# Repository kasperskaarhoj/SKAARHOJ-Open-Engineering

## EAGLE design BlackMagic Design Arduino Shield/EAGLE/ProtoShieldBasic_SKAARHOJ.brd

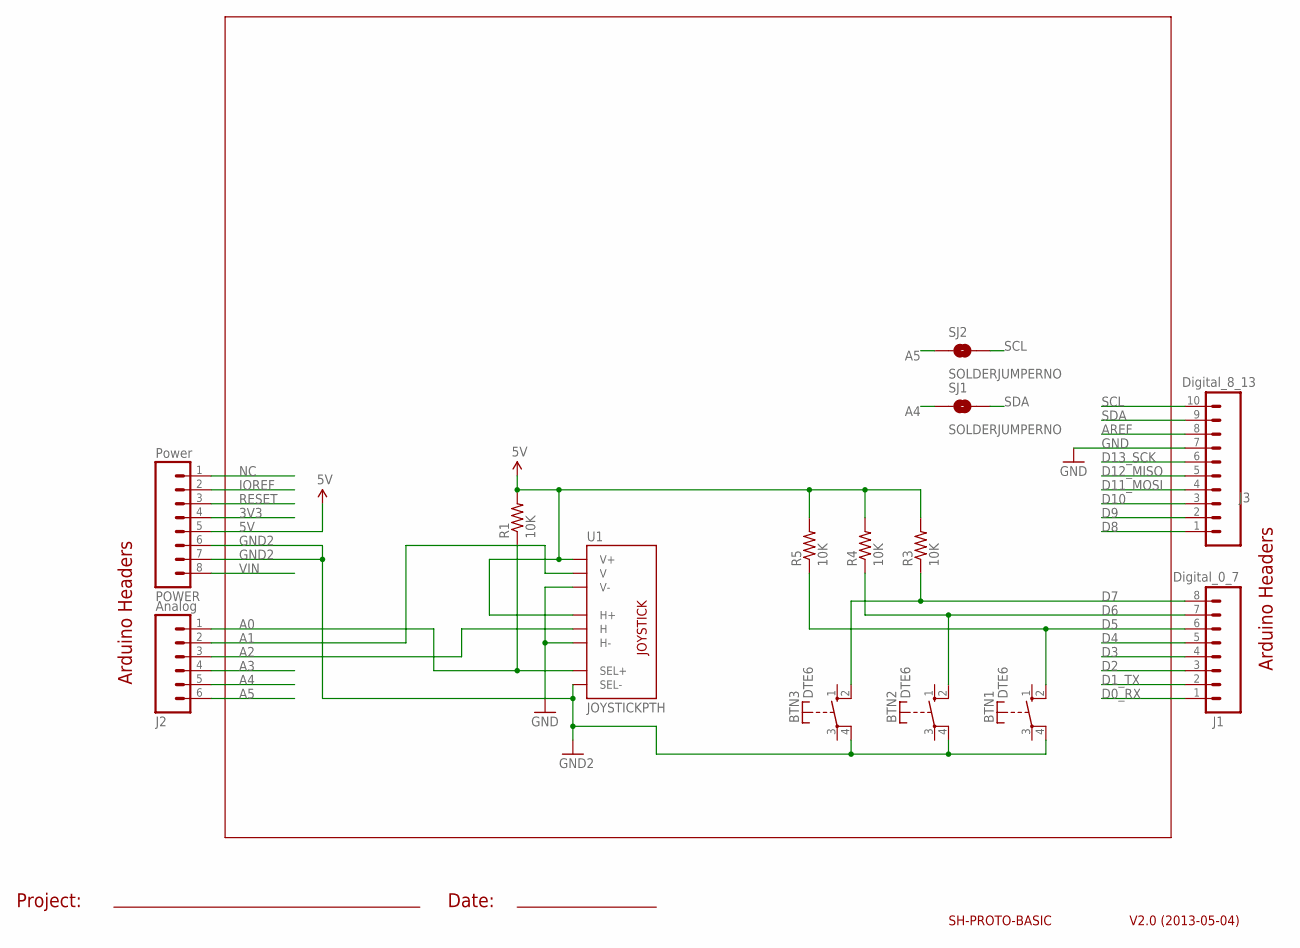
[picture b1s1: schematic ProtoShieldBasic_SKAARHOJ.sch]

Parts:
BTN1, BTN2, BTN3: DTE6
J1: Digital_0_7; 1X08
J2: Analog; 1X06
J3: Digital_8_13; 1X10
POWER: Power; 1X08
R1, R3, R4, R5: 10K; 0207/10
SJ1, SJ2: SOLDERJUMPERNO; SJ_2S-NO
U1: JOYSTICKPTH; JOYSTICK

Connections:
3V3: POWER.4
5V: POWER.5, R1.2, R3.2, R4.2, R5.2, U1.H1 (H+), U1.V1 (V+)
A0: J2.1, R1.1, U1.B1A (SEL+)
A1: J2.2, U1.V2 (V)
A2: J2.3, U1.H2 (H)
A3: J2.4
A4: J2.5, SJ1.1
A5: J2.6, SJ2.1
AREF: J3.8
D0_RX: J1.1
D1_TX: J1.2
D2: J1.3
D3: J1.4
D4: J1.5
D5: BTN1.2 (S), J1.6, R5.1
D6: BTN2.2 (S), J1.7, R4.1
D7: BTN3.2 (S), J1.8, R3.1
D8: J3.1
D9: J3.2
D10: J3.3
D11_MOSI: J3.4
D12_MISO: J3.5
D13_SCK: J3.6
GND: J3.7, U1.H3 (H-), U1.V3 (V-)
GND2: BTN1.4, BTN2.4, BTN3.4, POWER.6, POWER.7, U1.B2A (SEL-)
IOREF: POWER.2
NC: POWER.1
RESET: POWER.3
SCL: J3.10, SJ2.2
SDA: J3.9, SJ1.2
VIN: POWER.8

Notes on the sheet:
V2.0 (2013-05-04)
SH-PROTO-BASIC
Arduino Headers
Project:
Date:

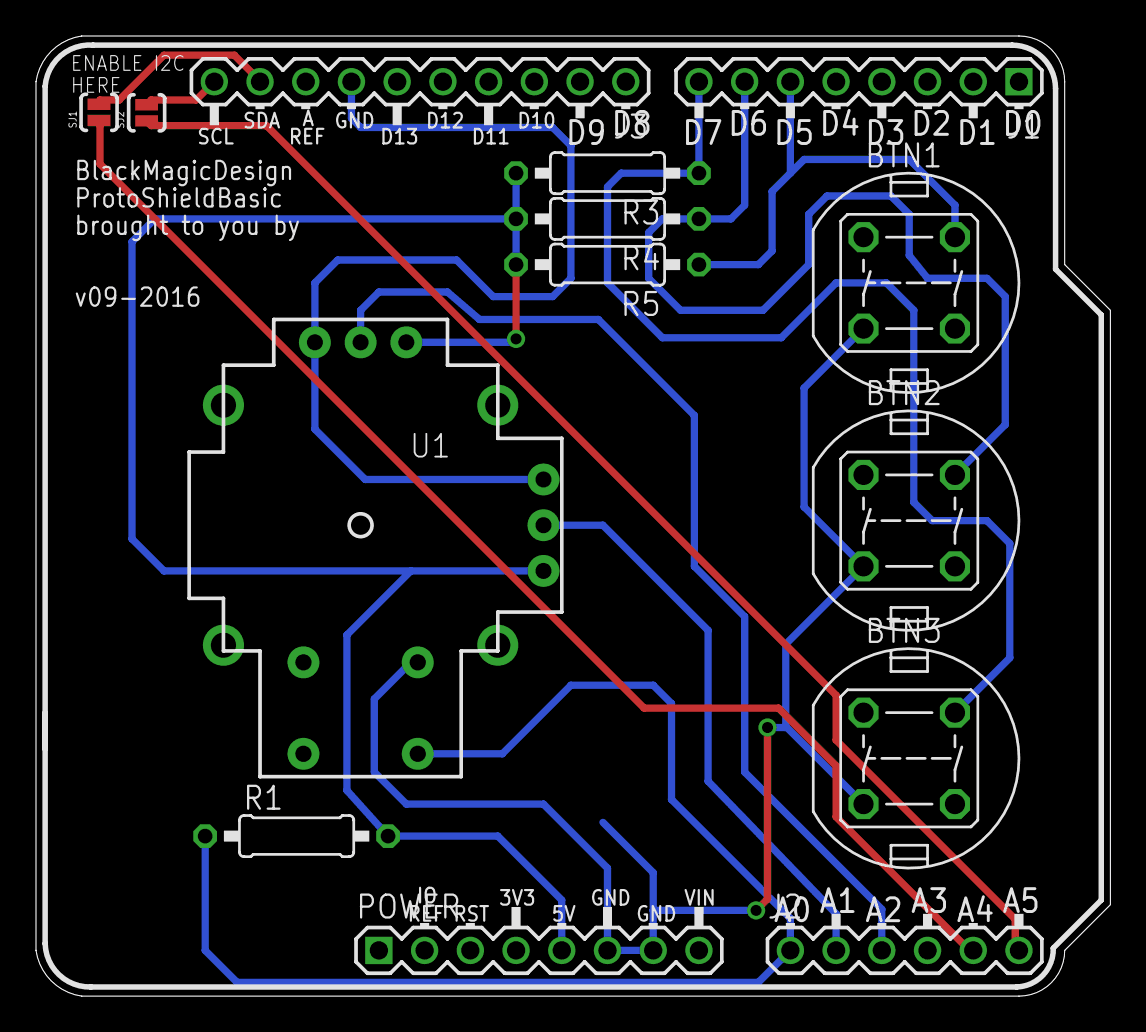
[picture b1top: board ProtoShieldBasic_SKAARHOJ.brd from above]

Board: 2 copper layers, 59.7 x 53.3 mm, 14 parts (0 on the bottom side), 13 nets.

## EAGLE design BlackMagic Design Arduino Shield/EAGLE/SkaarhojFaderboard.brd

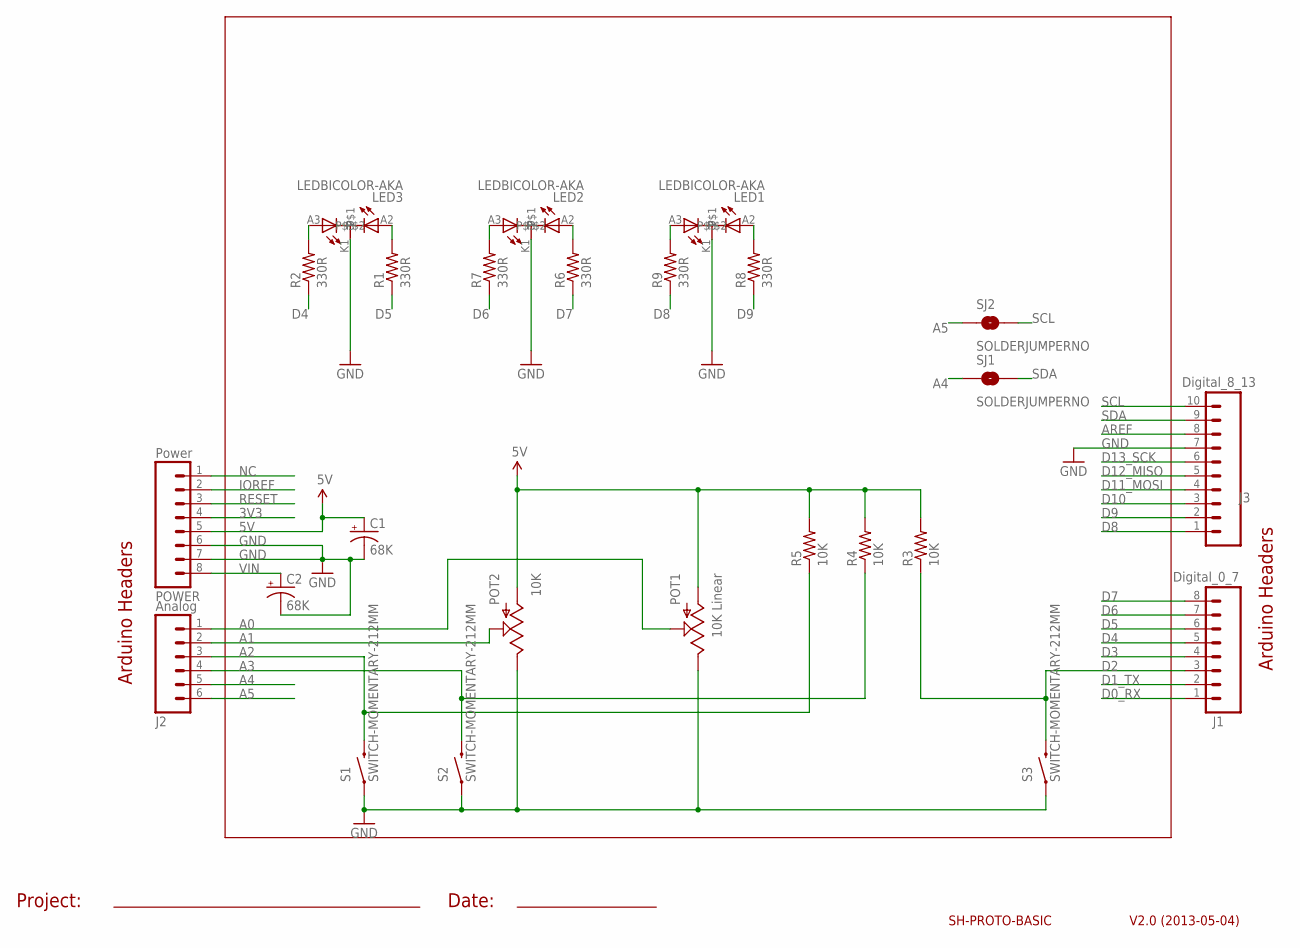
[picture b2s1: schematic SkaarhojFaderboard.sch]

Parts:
C1, C2: 68K; CPOL-RADIAL-100UF-25V
J1: Digital_0_7; 1X08
J2: Analog; 1X06
J3: Digital_8_13; 1X10
LED1, LED2, LED3: LEDBICOLOR-AKA; LED5MM-BICOLOR
POT1: 10K Linear; SLIDER20
POT2: 10K; ALPS_POT
POWER: Power; 1X08
R1, R2, R6, R7, R8, R9: 330R; 0207/10
R3, R4, R5: 10K; 0207/10
S1, S2, S3: SWITCH-MOMENTARY-212MM; TACTILE-PTH-12MM
SJ1, SJ2: SOLDERJUMPERNO; SJ_2S-NO

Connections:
3V3: POWER.4
5V: C1.1 (+), POT1.3 (A), POT2.P$3 (A), POWER.5, R3.2, R4.2, R5.2
A0: J2.1, POT1.2A (S)
A1: J2.2, POT2.P$2 (S)
A2: J2.3, R5.1, S1.3 (2)
A3: J2.4, R4.1, S2.3 (2)
A4: J2.5, SJ1.1
A5: J2.6, SJ2.1
AREF: J3.8
D0_RX: J1.1
D1_TX: J1.2
D2: J1.3, R3.1, S3.3 (2)
D3: J1.4
D4: J1.5, R2.1
D5: J1.6, R1.1
D6: J1.7, R7.1
D7: J1.8, R6.1
D8: J3.1, R9.1
D9: J3.2, R8.1
D10: J3.3
D11_MOSI: J3.4
D12_MISO: J3.5
D13_SCK: J3.6
GND: C1.2 (-), C2.2 (-), J3.7, LED1.K1, LED2.K1, LED3.K1, POT1.1 (E), POT2.P$1 (E), POWER.6, POWER.7, S1.1, S2.1, S3.1
IOREF: POWER.2
unnamed: LED2.A3, R7.2
unnamed: LED3.A3, R2.2
unnamed: LED2.A2, R6.2
unnamed: LED3.A2, R1.2
unnamed: LED1.A3, R9.2
unnamed: LED1.A2, R8.2
NC: POWER.1
RESET: POWER.3
SCL: J3.10, SJ2.2
SDA: J3.9, SJ1.2
VIN: C2.1 (+), POWER.8

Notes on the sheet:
V2.0 (2013-05-04)
SH-PROTO-BASIC
Arduino Headers
Project:
Date:

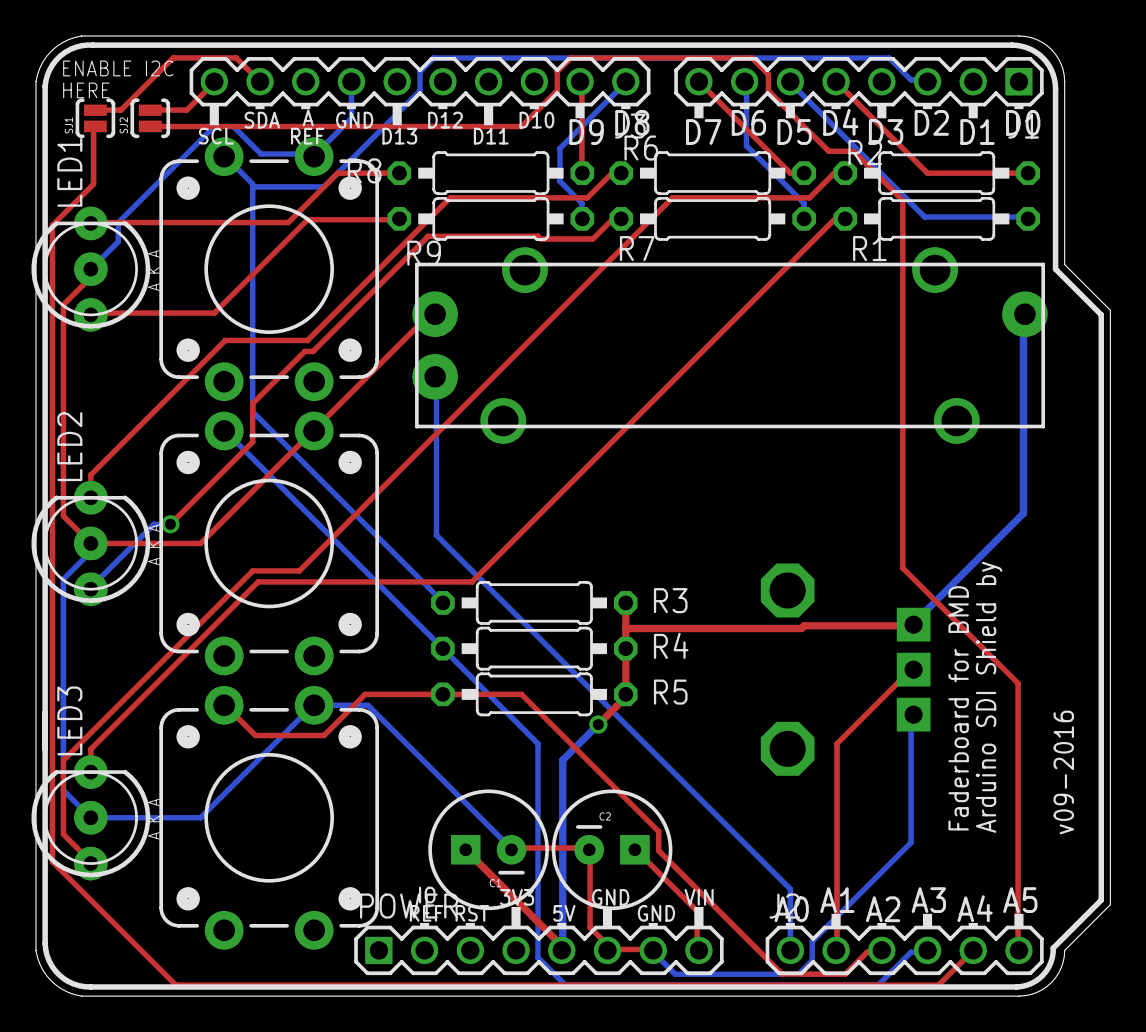
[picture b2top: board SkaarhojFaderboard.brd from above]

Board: 2 copper layers, 59.7 x 53.3 mm, 25 parts (0 on the bottom side), 24 nets.

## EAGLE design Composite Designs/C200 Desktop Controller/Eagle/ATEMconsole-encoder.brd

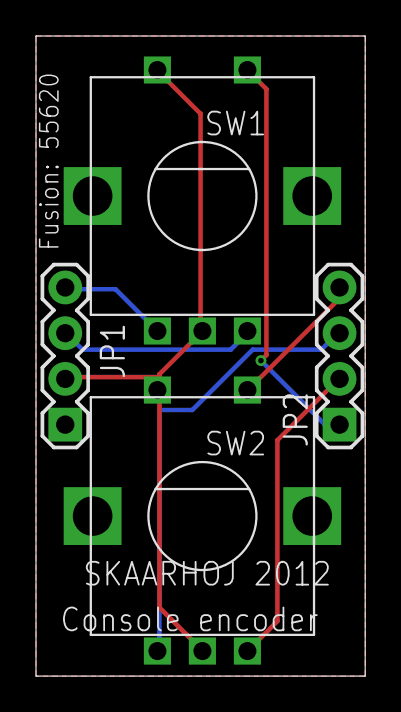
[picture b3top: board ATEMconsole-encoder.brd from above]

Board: 2 copper layers, 18.3 x 35.6 mm, 4 parts (0 on the bottom side), 7 nets.

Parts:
JP1, JP2: 1X04
SW1, SW2: EC12E_SW; ALPS_EC12E_SW

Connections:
5V: JP1.2, SW1.C, SW1.D, SW2.C, SW2.D
JP1: JP2.2, SW2.B
unnamed: JP1.3, SW1.B
unnamed: JP1.4, SW1.A
unnamed: JP2.1, SW1.E
unnamed: JP2.3, SW2.A
unnamed: JP2.4, SW2.E

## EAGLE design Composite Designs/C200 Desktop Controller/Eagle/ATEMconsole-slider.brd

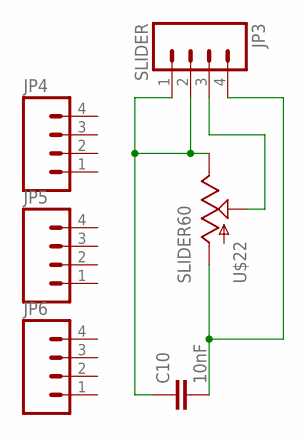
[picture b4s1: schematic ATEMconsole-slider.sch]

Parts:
C10: 10nF; AXIAL-5MM
JP3: SLIDER; 1X04
JP4, JP5, JP6: M04PTH; 1X04
U$22: SLIDER60

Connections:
unnamed: C10.P$1 (1), JP3.1, JP3.2, U$22.1 (E)
unnamed: C10.P$2 (2), JP3.4, U$22.3 (A)
unnamed: JP3.3, U$22.2A (S)

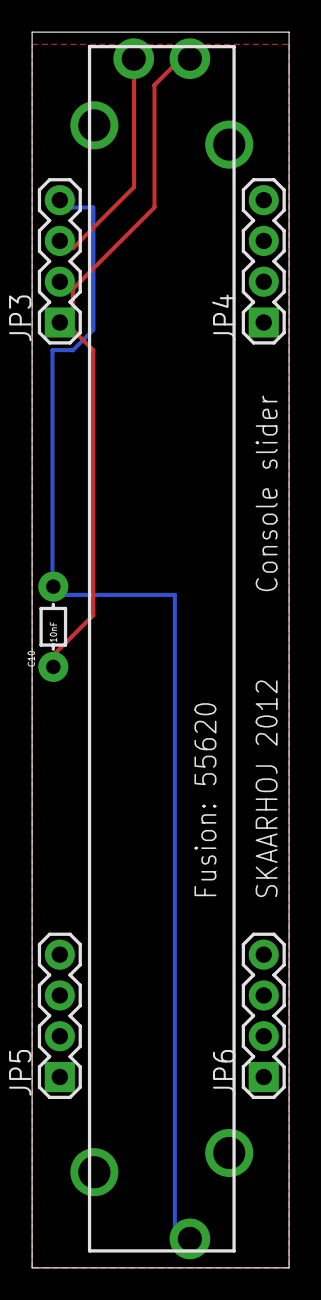
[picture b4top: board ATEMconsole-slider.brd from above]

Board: 2 copper layers, 16.0 x 77.0 mm, 6 parts (0 on the bottom side), 3 nets.

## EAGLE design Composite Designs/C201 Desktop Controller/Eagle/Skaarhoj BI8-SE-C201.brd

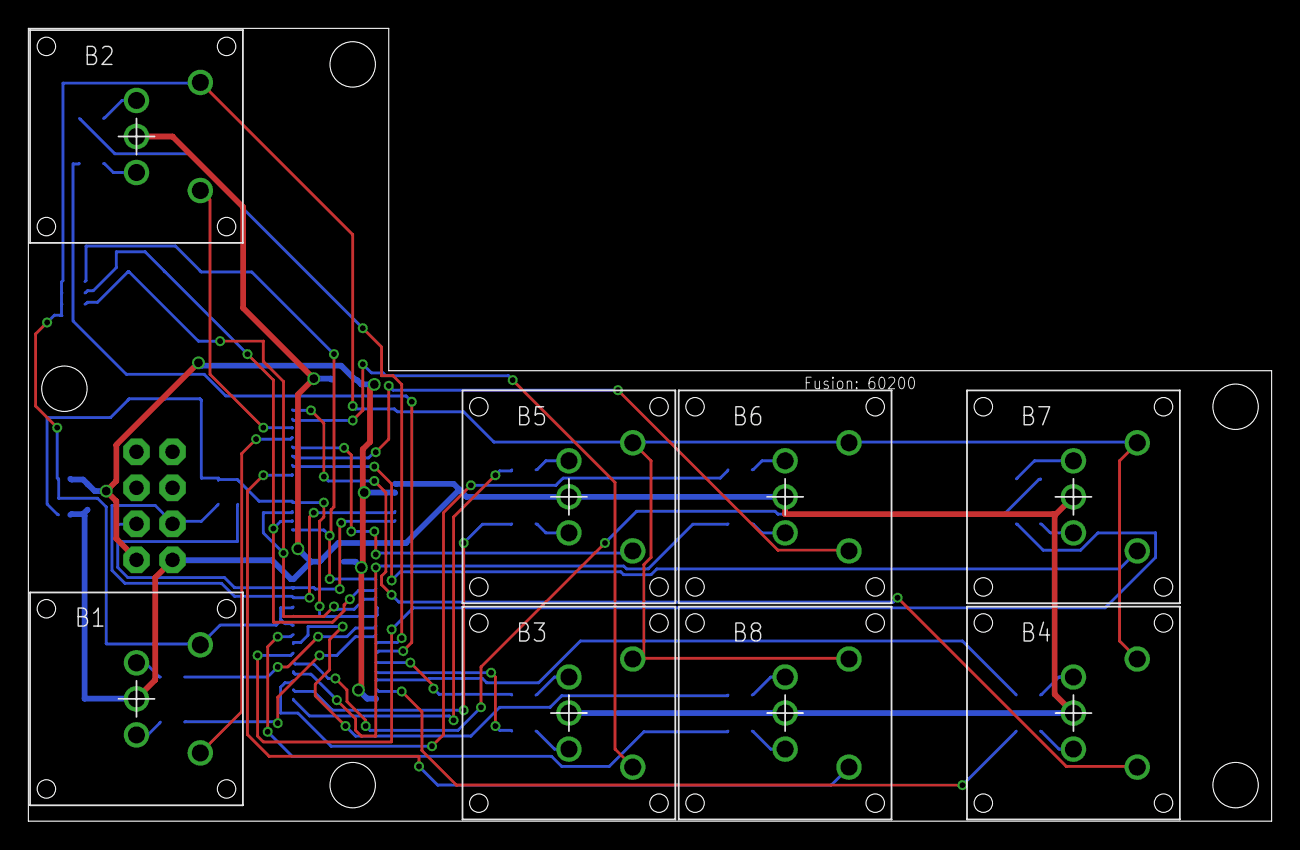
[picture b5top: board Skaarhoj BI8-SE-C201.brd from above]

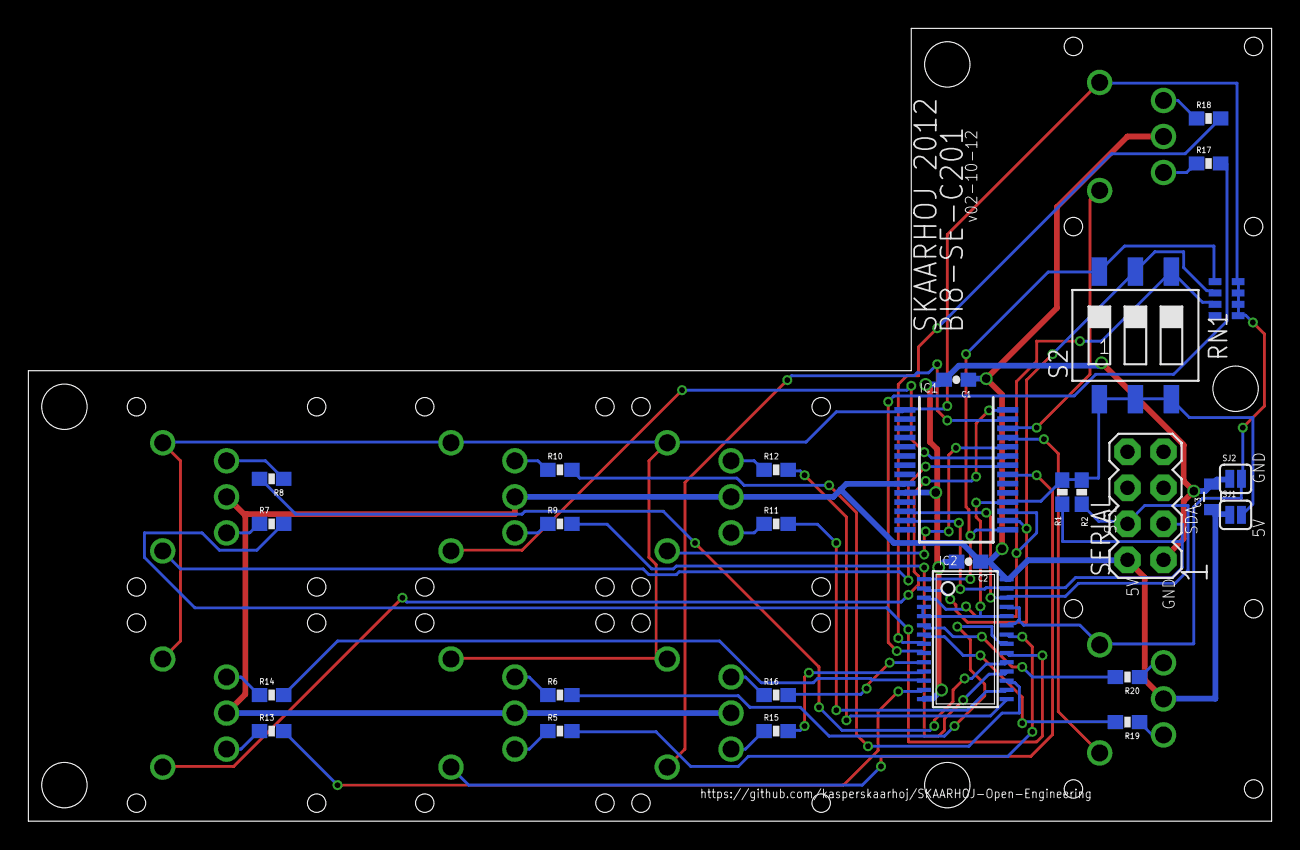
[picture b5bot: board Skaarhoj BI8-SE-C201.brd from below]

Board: 2 copper layers, 87.6 x 55.9 mm, 36 parts (28 on the bottom side), 49 nets.

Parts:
B1, B2, B3, B4, B5, B6, B7, B8: LP11-B"; LP11
C1, C2: 100nF; 0603-CAP
C3: 10uF; 0805
IC1: MCP23017SS; SSOP28
IC2: PCA9685; TSSOP28
R1, R2: 10K; 0603-RES
R5, R6, R7, R8, R9, R10, R11, R12, R13, R14, R15, R16, R17, R18, R19, R20: 270; 0603-RES
RN1: 10K; CAY16_HAND
S2: SWS003; SMS-003
SERIAL: M04X2; 2X4
SJ1, SJ2: SOLDERJUMPERNC; SJ_2S

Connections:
5V: B1.COM, B2.COM, B3.COM, B4.COM, B5.COM, B6.COM, B7.COM, B8.COM, C1.2, C2.1, C3.1, IC1.9, IC2.28, SERIAL.2, SJ1.1
5VL: IC1.18, IC2.4, IC2.5, IC2.24, R1.1, R2.1, S2.1, S2.2, S2.3, SJ1.2
A0: IC1.15, IC2.1, RN1.5, S2.6
A1: IC1.16, IC2.2, RN1.6, S2.5
A2: IC1.17, IC2.3, RN1.7, S2.4
GND: C1.1, C2.2, C3.2, IC1.10, IC2.14, SERIAL.1, SJ2.1
GNDL: B1.P$4, B2.P$4, B3.P$4, B4.P$4, B5.P$4, B6.P$4, B7.P$4, B8.P$4, IC1.1, IC2.23, IC2.25, RN1.1, RN1.2, RN1.3, RN1.4, SJ2.2
GPA0: B8.P$5, IC1.21
GPA1: B7.P$5, IC1.22
GPA2: B6.P$5, IC1.23
GPA3: B5.P$5, IC1.24
GPA4: B1.P$5, IC1.25
GPA5: B2.P$5, IC1.26
GPA6: B3.P$5, IC1.27
GPA7: B4.P$5, IC1.28
I2C_SCL: IC1.12, IC2.26, R2.2, SERIAL.4
I2C_SDA: IC1.13, IC2.27, R1.2, SERIAL.3
L0: B1.P$2, R20.1
L1: B1.P$3, R19.1
L2: B2.P$2, R18.1
L3: B2.P$3, R17.1
L4: B3.P$2, R16.1
L5: B3.P$3, R15.1
L6: B4.P$2, R14.1
L7: B4.P$3, R13.1
L8: B5.P$2, R12.1
L9: B5.P$3, R11.1
L10: B6.P$2, R10.1
L11: B6.P$3, R9.1
L12: B7.P$2, R8.1
L13: B7.P$3, R7.1
L14: B8.P$2, R6.1
L15: B8.P$3, R5.1
unnamed: IC2.13, R13.2
unnamed: IC2.12, R14.2
unnamed: IC2.11, R15.2
unnamed: IC2.10, R16.2
unnamed: IC2.9, R17.2
unnamed: IC2.8, R18.2
unnamed: IC2.7, R19.2
unnamed: IC2.6, R20.2
unnamed: IC2.15, R12.2
unnamed: IC2.16, R11.2
unnamed: IC2.17, R10.2
unnamed: IC2.18, R9.2
unnamed: IC2.19, R8.2
unnamed: IC2.20, R7.2
unnamed: IC2.21, R6.2
unnamed: IC2.22, R5.2

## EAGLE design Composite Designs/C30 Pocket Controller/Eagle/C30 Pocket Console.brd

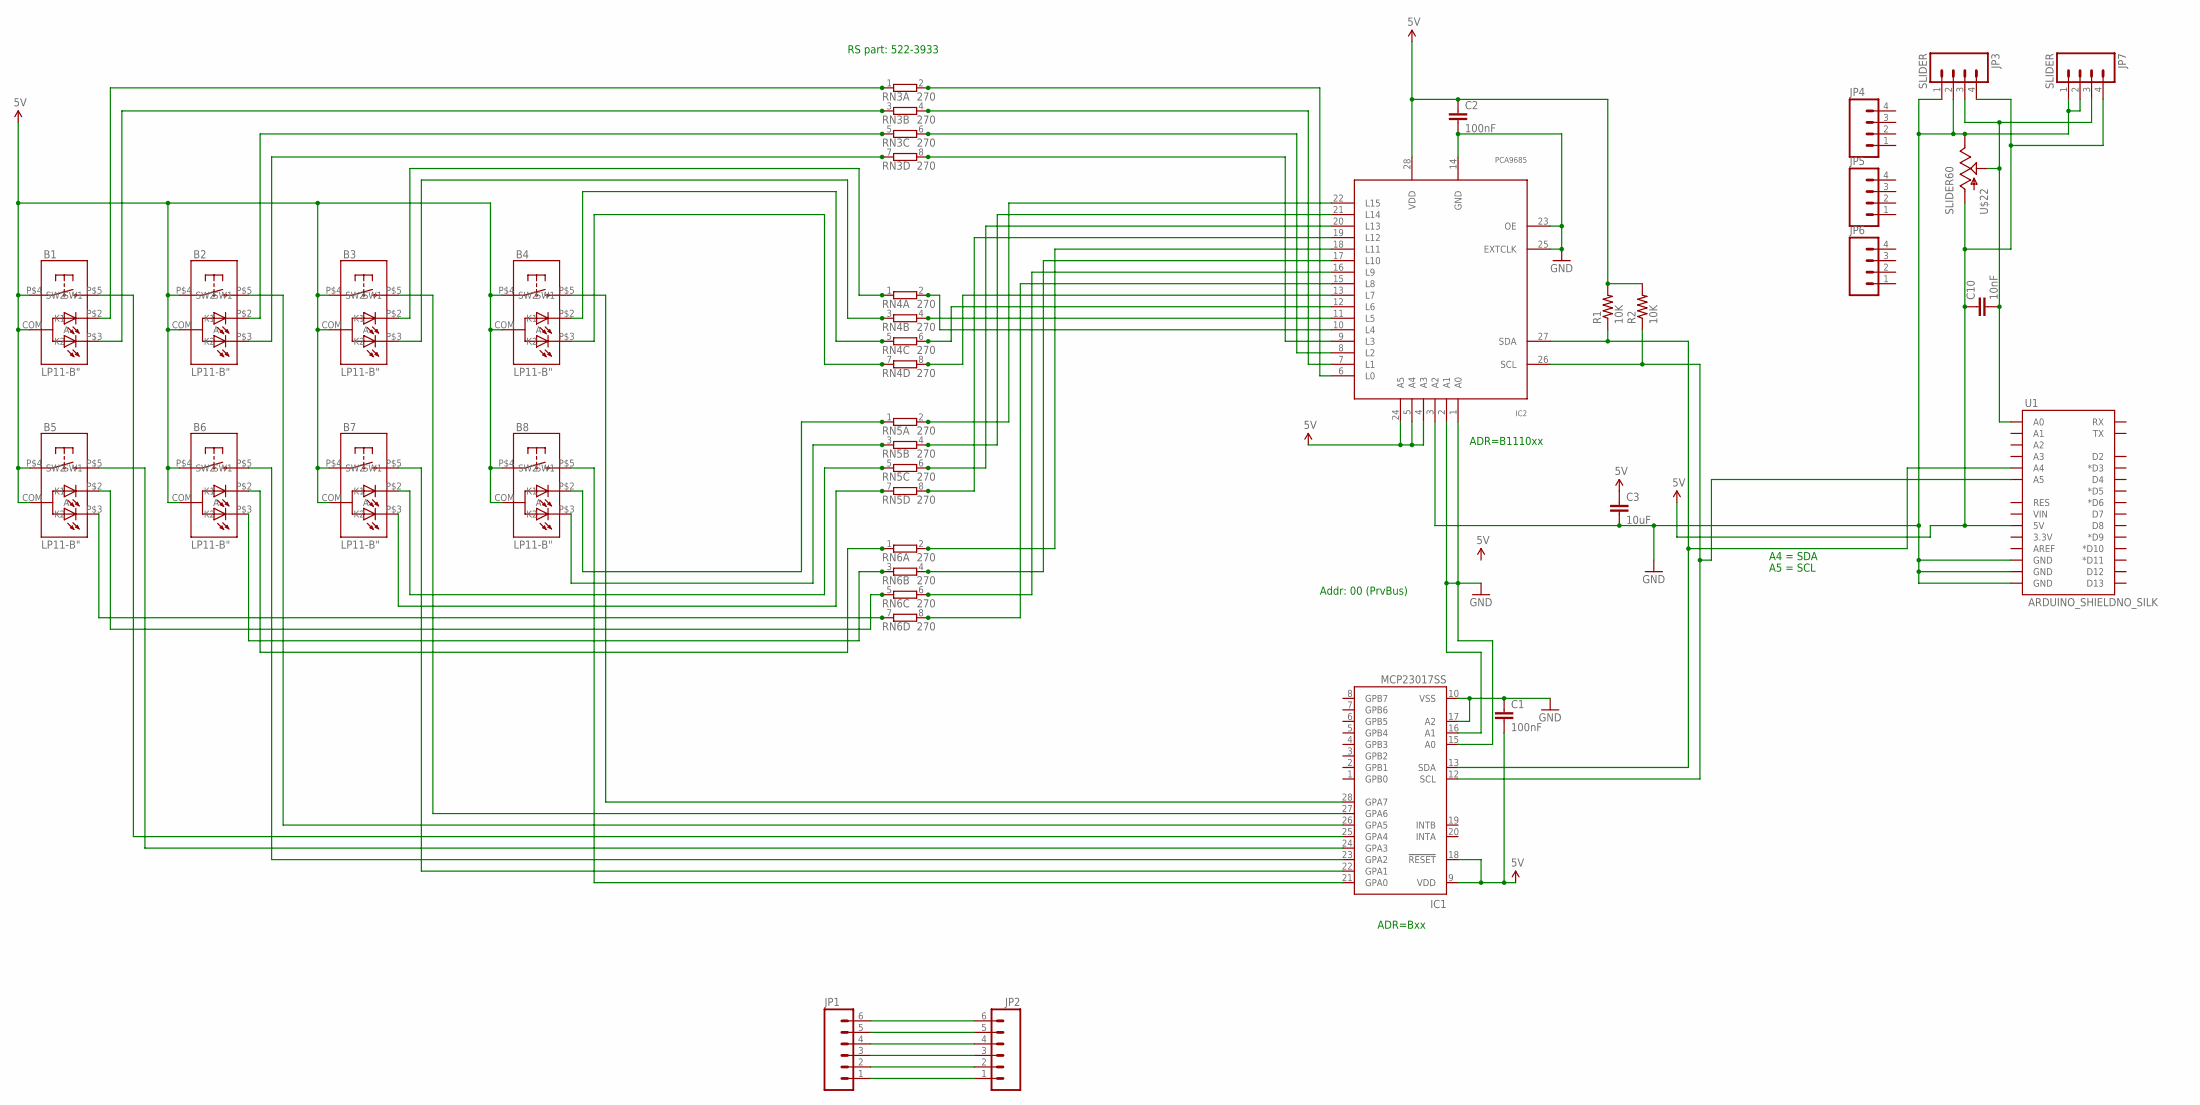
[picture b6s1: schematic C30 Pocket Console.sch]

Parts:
B1, B2, B3, B4, B5, B6, B7, B8: LP11-B"; LP11
C1, C2: 100nF; AXIAL-5MM
C3: 10uF; AXIAL-5MM
C10: 10nF; AXIAL-5MM
IC1: MCP23017SS; SSOP28; MPN MCP23017-E/SS
IC2: PCA9685; TSSOP28
JP1, JP2: M06POLAR; MOLEX-1X6
JP3, JP7: SLIDER; 1X04
JP4, JP5, JP6: M04PTH; 1X04
R1, R2: 10K; 0603-RES
RN3, RN4, RN5, RN6: 270; SIL8
U1: ARDUINO_SHIELDNO_SILK; DUEMILANOVE_VIAS
U$22: SLIDER60

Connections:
5V: B1.COM (A), B1.P$4 (SW1), B2.COM (A), B2.P$4 (SW1), B3.COM (A), B3.P$4 (SW1), B4.COM (A), B4.P$4 (SW1), B5.COM (A), B5.P$4 (SW1), B6.COM (A), B6.P$4 (SW1), B7.COM (A), B7.P$4 (SW1), B8.COM (A), B8.P$4 (SW1), C1.P$2 (2), C2.P$1 (1), C3.P$1 (1), C10.P$1 (1), IC1.9 (VDD), IC1.18 (!RESET), IC2.4 (A3), IC2.5 (A4), IC2.24 (A5), IC2.28 (VDD), JP3.4, JP7.4, R1.2, R2.2, U1.5V, U$22.3 (A)
GND: C1.P$1 (1), C2.P$2 (2), C3.P$2 (2), IC1.10 (VSS), IC1.15 (A0), IC1.16 (A1), IC1.17 (A2), IC2.1 (A0), IC2.2 (A1), IC2.3 (A2), IC2.14 (GND), IC2.23 (OE), IC2.25 (EXTCLK), JP3.1, JP3.2, JP7.1, JP7.2, U1.GND@0 (GND), U1.GND@1 (GND), U1.GND@2 (GND), U$22.1 (E)
unnamed: JP1.1, JP2.1
unnamed: B7.P$3 (K2), RN5.7 (1)
unnamed: JP1.2, JP2.2
unnamed: B2.P$2 (K1), RN3.5 (1)
unnamed: B2.P$3 (K2), RN3.7 (1)
unnamed: JP1.3, JP2.3
unnamed: B1.P$2 (K1), RN3.1
unnamed: B1.P$3 (K2), RN3.3 (1)
unnamed: IC2.6 (L0), RN3.2
unnamed: IC2.7 (L1), RN3.4 (2)
unnamed: IC2.8 (L2), RN3.6 (2)
unnamed: IC2.9 (L3), RN3.8 (2)
unnamed: IC2.10 (L4), RN4.2
unnamed: IC2.11 (L5), RN4.4 (2)
unnamed: IC2.12 (L6), RN4.6 (2)
unnamed: IC2.13 (L7), RN4.8 (2)
unnamed: B3.P$2 (K1), RN4.1
unnamed: B3.P$3 (K2), RN4.3 (1)
unnamed: B4.P$2 (K1), RN4.5 (1)
unnamed: B4.P$3 (K2), RN4.7 (1)
unnamed: IC2.19 (L12), RN5.8 (2)
unnamed: IC2.20 (L13), RN5.6 (2)
unnamed: IC2.21 (L14), RN5.4 (2)
unnamed: IC2.22 (L15), RN5.2
unnamed: IC2.15 (L8), RN6.8 (2)
unnamed: IC2.16 (L9), RN6.6 (2)
unnamed: IC2.17 (L10), RN6.4 (2)
unnamed: IC2.18 (L11), RN6.2
unnamed: B5.P$3 (K2), RN6.7 (1)
unnamed: B5.P$2 (K1), RN6.5 (1)
unnamed: B6.P$3 (K2), RN6.3 (1)
unnamed: B6.P$2 (K1), RN6.1
unnamed: JP1.4, JP2.4
unnamed: JP1.5, JP2.5
unnamed: B8.P$3 (K2), RN5.3 (1)
unnamed: B8.P$2 (K1), RN5.1
unnamed: B1.P$5 (SW2), IC1.25 (GPA4)
unnamed: B5.P$5 (SW2), IC1.24 (GPA3)
unnamed: B6.P$5 (SW2), IC1.23 (GPA2)
unnamed: B2.P$5 (SW2), IC1.26 (GPA5)
unnamed: B8.P$5 (SW2), IC1.21 (GPA0)
unnamed: B7.P$5 (SW2), IC1.22 (GPA1)
unnamed: B4.P$5 (SW2), IC1.28 (GPA7)
unnamed: B3.P$5 (SW2), IC1.27 (GPA6)
unnamed: JP1.6, JP2.6
unnamed: B7.P$2 (K1), RN5.5 (1)
unnamed: IC1.12 (SCL), IC2.26 (SCL), R2.1, U1.A5
unnamed: IC1.13 (SDA), IC2.27 (SDA), R1.1, U1.A4
unnamed: C10.P$2 (2), JP3.3, JP7.3, U1.A0, U$22.2A (S)

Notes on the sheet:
A5 = SCL
A4 = SDA
ADR=B1110xx
ADR=Bxx
Addr: 00 (PrvBus)
RS part: 522-3933

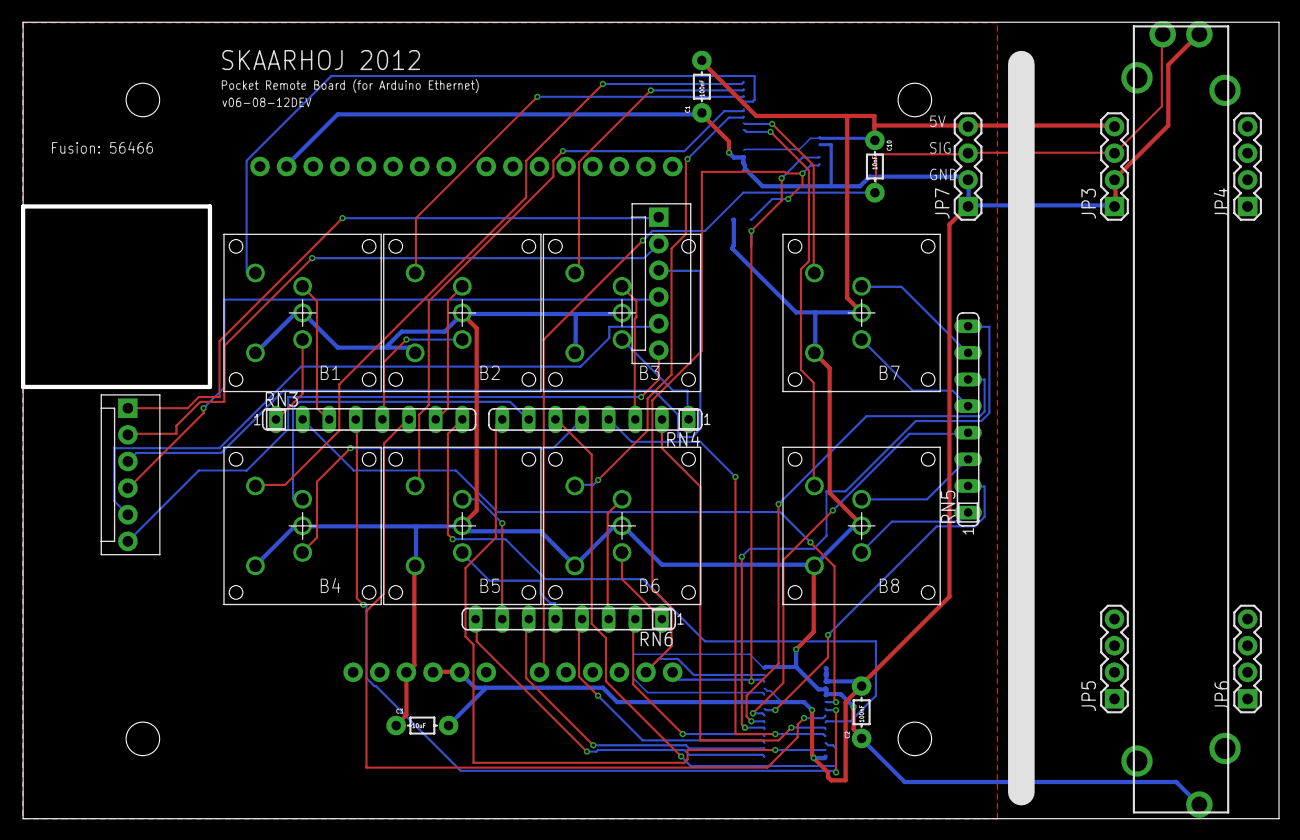
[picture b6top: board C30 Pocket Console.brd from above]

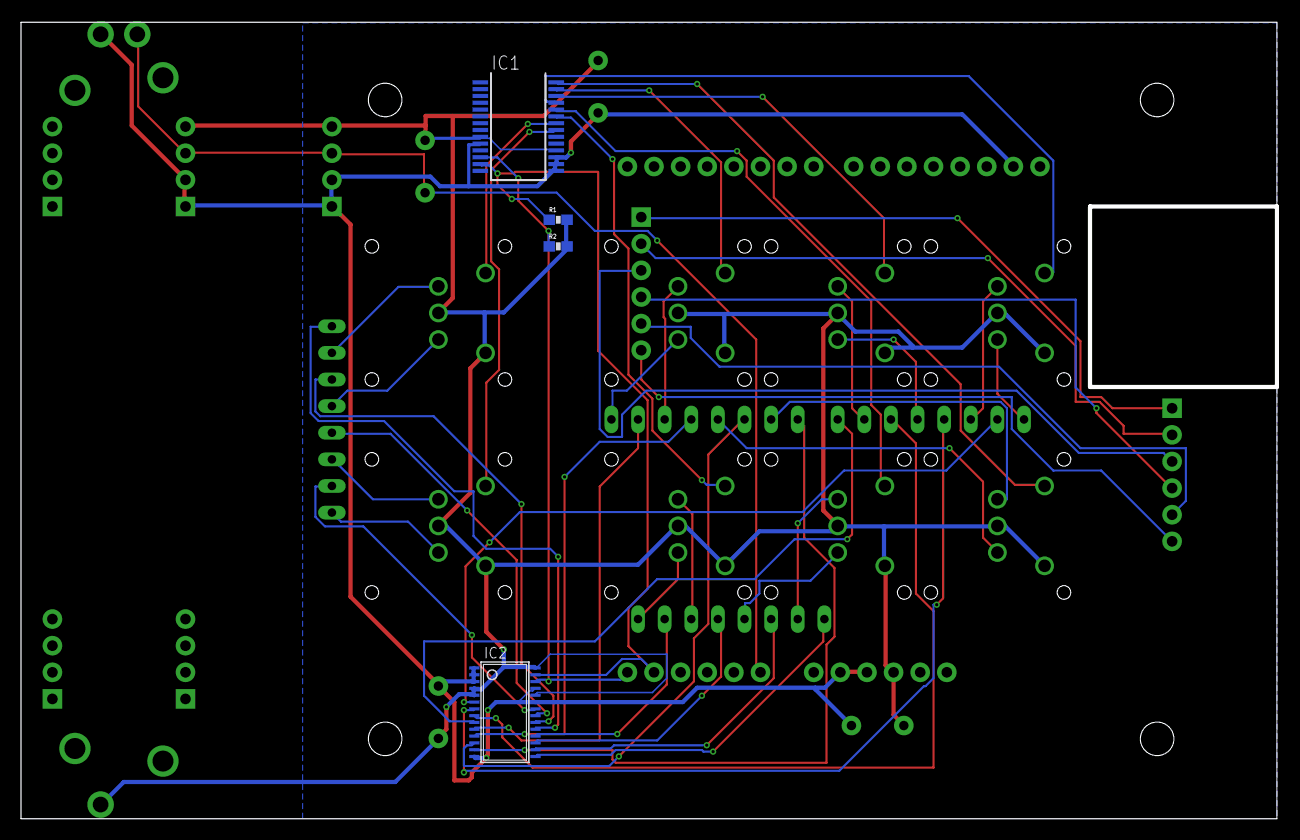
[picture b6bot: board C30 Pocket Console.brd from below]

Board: 2 copper layers, 119.8 x 76.0 mm, 29 parts (4 on the bottom side), 51 nets.

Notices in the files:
parts and their libraries:
SparkFun-Electromechanical: Licensing: Creative Commons ShareAlike 4.0 International - https://creativecommons.org/licenses/by-sa/4.0
SparkFun: Licensing: CC v3.0 Share-Alike You are welcome to use this library for commercial purposes.
